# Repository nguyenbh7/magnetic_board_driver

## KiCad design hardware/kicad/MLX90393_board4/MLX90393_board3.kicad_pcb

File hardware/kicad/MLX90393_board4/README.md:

# MLX90393 4×4 Hall sensor PCB — source KiCad project

This directory is the designated version-controlled home for the **editable**
MLX90393 board project supplied by the lab. The original user-uploaded source
archive was `MLX90393_board4.zip` (ChatGPT Library upload 2026-09-25).
**Inside that ZIP the source project is still named `MLX90393_board3`.**
Preserve the filenames rather than renaming schematic references.

## Provenance and current upload state

Source ZIP SHA-256:
`32363b1b48f097b6289367b30ce883349a952ba2ddef2e18a702d23629b0fb12`.

A curated source-only ZIP has been prepared for local extraction into
`hardware/kicad/MLX90393_board4/`. It contains **21 source/library files**
(about 1.28 MB uncompressed, 265 KB compressed):
`MLX90393_board3.kicad_pro`,
`MLX90393_board3.kicad_pcb`,
`MLX90393_board3.kicad_sch`,
`MLX_array.kicad_sch`, `fp-lib-table`, `sym-lib-table`,
local `.kicad_sym` symbol files, `Footprints/`, `JLCPCB_lib/`
footprint/symbol/3D libraries, and `Addafruit.pretty/`.

**Important:** This documentation was committed directly to GitHub.
The **large KiCad source files themselves require the local Git push**
described below; do not assume they are already in Git because this README
exists. Do not commit the original archive's backups, `.kicad_prl`,
lock/autosave files, cache files, Gerbers, drill plots, or generated
manufacturing ZIPs. The editable project files are the source of truth.

### Install the source-only ZIP on the Windows development machine

1. Download `MLX90393_board4_git_source.zip` from the ChatGPT
   deliverable and save it to `$HOME\Downloads`.
2. From PowerShell:

```powershell
Set-Location 'F:\GitHub\magnetic_board_driver'
git switch feature/live-rigid-body-fit
git pull --ff-only
Expand-Archive -LiteralPath "$HOME\Downloads\MLX90393_board4_git_source.zip" -DestinationPath . -Force
git status --short -- hardware/kicad
git add hardware/kicad
git commit -m "Add editable MLX90393 board KiCad source and local footprint libraries"
git push
```

3. Open `hardware/kicad/MLX90393_board4/MLX90393_board3.kicad_pro`
   in KiCad 9. Review missing library/model warnings and compare
   against the **actual fabricated October 23 PCB revision**.
   The ZIP is selected source files, not a full backup of the
   original 10-MB archive.

## What the archived PCB supports

The populated `MLX90393_board3.kicad_pcb` has **16**
`MLX90393-01x` QFN-16 sensor footprints `M1–M16` on
**F.Cu**, all with `(at x y 180)`, on a regular
**4×4 array of 4.5-mm pitch**. Connector footprints
`J1–J3` are near the PCB's low-Y edge (native
KiCad coordinates approximately Y=82.9 mm), with
sensor centers around Y=118.4–131.9 mm. Four mounting
holes `H1–H4` are included. These are **KiCad layout
coordinates**, not patient DICOM coordinates or firmware
sensor-index evidence.

Current Rust `data_transfer/src/rpc.rs:SENSOR_POSITIONS_MM`
uses acquisition indices increasing by +Y first and then +X.
The source layout's reference designators `M1–M16` do not
automatically establish which footprint is firmware index 0;
trace the I²C addresses and design nets independently.

## Package axis orientation (provisional)

Melexis' **Figure 26** QFN top view shows
**pin 1 toward the upper-right**, with package **+X up,
+Y left, +Z outward**. Its separate **Figure 27**
pinout illustrates **pin 1 at bottom-left**, a view
rotated 180° in plane; do not transfer axis arrows
without rotating the view. The KiCad footprint's
**pad 1 is lower-left in the 0° footprint library**;
all 16 mounted footprints are rotated **180° on
F.Cu**, making pad 1 **upper-right in native KiCad
top view**, matching Figure 26.

Therefore the provisional **package axes in native
KiCad top view** are +X **toward decreasing PCB Y**
(toward JST), +Y **toward decreasing PCB X**,
and +Z **out of the F.Cu face**.

**Correction from the populated board and current firmware:**
`data_transfer/src/rpc.rs` explicitly diagrams
`0 4 8 12` on the **bottom row with JST down**,
i.e. firmware sensor 0 is **bottom-left**, not
bottom-right. Firmware +X points picture-right
(toward decreasing native KiCad X once viewed
with JST down), +Y away from JST (toward
increasing native KiCad Y), and +Z toward the
chip-facing viewer. The previous CT candidate
`gk_ct_sensor_order_proposal_v1` mistakenly
used sensor 0 at bottom-right and must be
replaced by the guarded `v2` mapping.

The KiCad footprint and manufacturer QFN axis
orientation then give the **provisional proper
chip-to-board field transform**:

```text
[B_grid_X, B_grid_Y, B_grid_Z] =
    [B_chip_Y, -B_chip_X, B_chip_Z]

M_chip_to_grid = [[0,1,0],[-1,0,0],[0,0,1]]
det(M_chip_to_grid) = +1
```

This agrees with the existing A1-style
`[By, -Bx, Bz]` transform in the Rust analysis
for this same chip/board convention. It remains
**unverified for actual October mounted
boards**, for the reasons below.

This matrix is **not yet validated against the actual
installed board, flashed firmware, or measured known
signed field**. For the CBCT application,
`B_LPS_candidate = R_grid_to_LPS @ M_chip_to_grid @ B_raw`,
with each board's scan-specific CT grid rotation.
Do **not** insert these candidate matrices into a
live `RigidProfile` as verified.

Melexis primary references: `MLX90393 Datasheet`
QFN-16 package/sensitive spot and pinout, figures 26–27;
`MLX90393 Getting Started Guide`, Figure 2
(MLX90393 QFN axis definition). Verify the actual
package designation before using this convention.

Further evidence and scan-specific geometry:
`hall-effect-motion-tracking/tools/cbct_bridge/HALL_AXIS_PROVENANCE.md`.

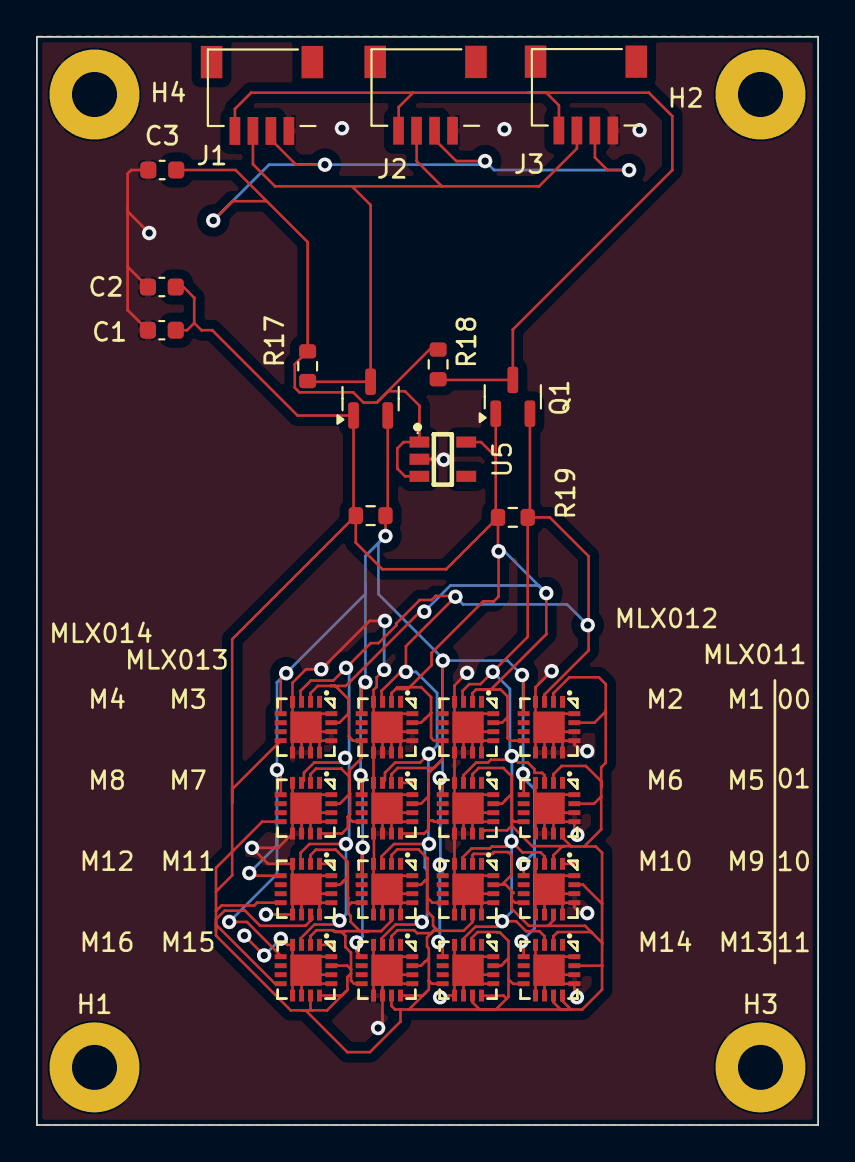
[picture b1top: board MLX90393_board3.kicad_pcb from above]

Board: 2 copper layers, 43.4 x 60.5 mm, 33 parts (0 on the bottom side), 7 nets.

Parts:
C1, C3: 10uF; C_0603_1608Metric
C2: 0.1uF; C_0603_1608Metric
H1, H2, H3, H4: MountingHole_Pad; MountingHole_2.5mm_Pad
J1, J2, J3: JST Conn_01x04; JST-PinHeader_1x04_P1.00mm_SMD
M1, M5, M9, M13: MLX90393-011; QFN-16_L3.0-W3.0-P0.50-BL-EP1.7
M2, M6, M10, M14: MLX90393-012; QFN-16_L3.0-W3.0-P0.50-BL-EP1.7
M3, M7, M11, M15: MLX90393-013; QFN-16_L3.0-W3.0-P0.50-BL-EP1.7
M4, M8, M12, M16: MLX90393-014; QFN-16_L3.0-W3.0-P0.50-BL-EP1.7
Q1, Q2: BSS138; SOT-23
R17, R18, R19, R20: 10k; R_0603_1608Metric
U5: AP2112K-3.3; SOT-25-5_L2.9-W1.6-P0.95-LS2.8-BL

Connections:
+3.3V: C1.1, C2.1, M1.2 (SENB/CS), M1.8 (VDD_IO), M1.15 (VDD), M2.2 (SENB/CS), M2.8 (VDD_IO), M2.15 (VDD), M3.2 (SENB/CS), M3.8 (VDD_IO), M3.15 (VDD), M4.2 (SENB/CS), M4.8 (VDD_IO), M4.15 (VDD), M5.2 (SENB/CS), M5.8 (VDD_IO), M5.12 (A0), M5.15 (VDD), M6.2 (SENB/CS), M6.8 (VDD_IO), M6.12 (A0), M6.15 (VDD), M7.2 (SENB/CS), M7.8 (VDD_IO), M7.12 (A0), M7.15 (VDD), M8.2 (SENB/CS), M8.8 (VDD_IO), M8.12 (A0), M8.15 (VDD), M9.2 (SENB/CS), M9.8 (VDD_IO), M9.11 (A1), M9.15 (VDD), M10.2 (SENB/CS), M10.8 (VDD_IO), M10.11 (A1), M10.15 (VDD), M11.2 (SENB/CS), M11.8 (VDD_IO), M11.11 (A1), M11.15 (VDD), M12.2 (SENB/CS), M12.8 (VDD_IO), M12.11 (A1), M12.15 (VDD), M13.2 (SENB/CS), M13.8 (VDD_IO), M13.11 (A1), M13.12 (A0), M13.15 (VDD), M14.2 (SENB/CS), M14.8 (VDD_IO), M14.11 (A1), M14.12 (A0), M14.15 (VDD), M15.2 (SENB/CS), M15.8 (VDD_IO), M15.11 (A1), M15.12 (A0), M15.15 (VDD), M16.2 (SENB/CS), M16.8 (VDD_IO), M16.11 (A1), M16.12 (A0), M16.15 (VDD), Q1.1 (G), Q2.1 (G), R19.1, R20.1, U5.5 (VOUT)
GND: C1.2, C2.2, C3.2, H1.1, H2.1, H3.1, H4.1, J1.1, J2.1, J3.1, M1.4 (NC), M1.9 (NC), M1.10 (NC), M1.11 (A1), M1.12 (A0), M1.13 (VSS), M1.14 (NC), M1.16 (NC), M1.17 (EP), M2.4 (NC), M2.9 (NC), M2.10 (NC), M2.11 (A1), M2.12 (A0), M2.13 (VSS), M2.14 (NC), M2.16 (NC), M2.17 (EP), M3.4 (NC), M3.9 (NC), M3.10 (NC), M3.11 (A1), M3.12 (A0), M3.13 (VSS), M3.14 (NC), M3.16 (NC), M3.17 (EP), M4.4 (NC), M4.9 (NC), M4.10 (NC), M4.11 (A1), M4.12 (A0), M4.13 (VSS), M4.14 (NC), M4.16 (NC), M4.17 (EP), M5.4 (NC), M5.9 (NC), M5.10 (NC), M5.11 (A1), M5.13 (VSS), M5.14 (NC), M5.16 (NC), M5.17 (EP), M6.4 (NC), M6.9 (NC), M6.10 (NC), M6.11 (A1), M6.13 (VSS), M6.14 (NC), M6.16 (NC), M6.17 (EP), M7.4 (NC), M7.9 (NC), M7.10 (NC), M7.11 (A1), M7.13 (VSS), M7.14 (NC), M7.16 (NC), M7.17 (EP), M8.4 (NC), M8.9 (NC), M8.10 (NC), M8.11 (A1), M8.13 (VSS), M8.14 (NC), M8.16 (NC), M8.17 (EP), M9.4 (NC), M9.9 (NC), M9.10 (NC), M9.12 (A0), M9.13 (VSS), M9.14 (NC), M9.16 (NC), M9.17 (EP), M10.4 (NC), M10.9 (NC), M10.10 (NC), M10.12 (A0), M10.13 (VSS), M10.14 (NC), M10.16 (NC), M10.17 (EP), M11.4 (NC), M11.9 (NC), M11.10 (NC), M11.12 (A0), M11.13 (VSS), M11.14 (NC), M11.16 (NC), M11.17 (EP), M12.4 (NC), M12.9 (NC), M12.10 (NC), M12.12 (A0), M12.13 (VSS), M12.14 (NC), M12.16 (NC), M12.17 (EP), M13.4 (NC), M13.9 (NC), M13.10 (NC), M13.13 (VSS), M13.14 (NC), M13.16 (NC), M13.17 (EP), M14.4 (NC), M14.9 (NC), M14.10 (NC), M14.13 (VSS), M14.14 (NC), M14.16 (NC), M14.17 (EP), M15.4 (NC), M15.9 (NC), M15.10 (NC), M15.13 (VSS), M15.14 (NC), M15.16 (NC), M15.17 (EP), M16.4 (NC), M16.9 (NC), M16.10 (NC), M16.13 (VSS), M16.14 (NC), M16.16 (NC), M16.17 (EP), U5.2 (GND)
SCL: J1.4, J2.4, J3.4, Q1.3 (D), R18.2
SCL_3V: M1.3 (SCL/SCLK), M2.3 (SCL/SCLK), M3.3 (SCL/SCLK), M4.3 (SCL/SCLK), M5.3 (SCL/SCLK), M6.3 (SCL/SCLK), M7.3 (SCL/SCLK), M8.3 (SCL/SCLK), M9.3 (SCL/SCLK), M10.3 (SCL/SCLK), M11.3 (SCL/SCLK), M12.3 (SCL/SCLK), M13.3 (SCL/SCLK), M14.3 (SCL/SCLK), M15.3 (SCL/SCLK), M16.3 (SCL/SCLK), Q1.2 (S), R19.2
SDA: J1.3, J2.3, J3.3, Q2.3 (D), R17.2
SDA_3V: M1.5 (SDA/MOSI), M2.5 (SDA/MOSI), M3.5 (SDA/MOSI), M4.5 (SDA/MOSI), M5.5 (SDA/MOSI), M6.5 (SDA/MOSI), M7.5 (SDA/MOSI), M8.5 (SDA/MOSI), M9.5 (SDA/MOSI), M10.5 (SDA/MOSI), M11.5 (SDA/MOSI), M12.5 (SDA/MOSI), M13.5 (SDA/MOSI), M14.5 (SDA/MOSI), M15.5 (SDA/MOSI), M16.5 (SDA/MOSI), Q2.2 (S), R20.2
VCC: C3.1, J1.2, J2.2, J3.2, R17.1, R18.1, U5.1 (VIN), U5.3 (EN)
